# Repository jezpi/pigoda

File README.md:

# pigoda - Introduction
Sensing station project on Raspberry Pi. The project is divided into
software and hardware. The software parts consist of 3 main bits:
daemon called *mqtt_rpi* which runs on raspberry Pi and is used to
send statistics. Application called *mqtt_channel* used to collect
sent statistcs. And the plotting software which are basically shell/python
scripts. The hardware part includes board designs as well as designs of 3D 
printed parts (n/a yet). Everything works via *MQTT* protocol. An example
of MQTT client is available in 

## The software
The standard installation assumes that You have an access to MQTT broker and a
VPS or something like that to collect the statistics. Since I use rrdtool as a plotting
library the statistics require continuity. You should provide a stable connection with accetable
latency (can't be too slow). It is not recommended to run *mqtt_channel* on the same raspberry Pi
where You run *mqtt_rpi* because of SD card overload (It could simply kill Your
SD card). 
### mqtt_rpi
#### Introduction

mqtt_rpi is a broker client as all software pieces written here.
         it sends statistics from previously configured gpios/i2c devices
	 specified in a config file *mqtt_rpi.yaml*. Also it handles some
         basic commands including relay switch on and off.
#### Usage
Normally it is supposed to be invoked via startscript placed in */etc/init.d/pigoda*
It has few useful command line options described below. 
-V Prints build date and time usage() information and then exits with exit(2) code EX_USAGE.
-c Path to config file. If not defined defaults to <code>/etc/mqtt_rpi.yaml</code>
-v Verbose mode. (not implemented yet)
-d Debug mode. (Ditto)
-f Stay in foreground

#### Config file directives:

An example config file included below:
```yaml

%YAML 1.1
---
pidfile: "/var/run/mqtt_rpi.pid"
logfile: "/var/log/mqtt_rpi.log"
debug: 4
daemon: false
delay: 5000000
identity: "mrpi_pooler"
mqtt_host: "localhost"
mqtt_port: 1883
mqtt_user: "mqtt_rpi"
mqtt_password: "CHANGE_ME"
mqtt_keepalive: 120
# configuration of channels
sensors:
        - name: "tempin"
          type: "ds18b20"
          address: "28-00000XXXXXXX"
          channel: "/environment/tempin"
        - name: "tempout"
          type: "ds18b20"
          address: "28-0000XXXXXXXX"
          channel: "/environment/tempout"
        - name: "pressure"
          type: "i2c"
          i2ctype: "bmp85"
          channel: "/environment/pressure"
        - name: "light"
          type: "i2c"
          i2ctype: "pcf8591"
          address: "0x48"
          config: "0"
          channel: "/environment/light"
gpio:
        - name: "green_led"
          gpio_pin: 2
          type: "failure"
        - name: "red_led"
          gpio_pin: 0
          type: "notify"
        - name: "pir_case"
          gpio_pin: 6
          type: "pir_sensor"
        - name: "power button"
          type: "pwr_btn"
          gpio_pin: 5

...

```
Let's describe first set and meaning of system related variables

Variable name | Possible values | Description
--------------|-----------------|------------
pidfile	      | STRING | Includes a valid path in \*NIX like system. Defaults to  > /var/run/mqtt_rpi.pid
logfile       | STRING | Defaults to "/var/log/mqtt_rpi.log"
debug         | NUMERIC | When greater than 0 activates extra debug messages
daemon        | BOOL | daemon mode
delay         | NUMERIC | Defines delay in a pooling loop. Defaults to 5000000

Other variables are related to MQTT connection, like identity user and password used to authenticate on a remote mqtt_host

Variable name | Possible values | Description
--------------|-----------------|------------
identity | STRING | Change this variable in case of having more than one station.
mqtt_host| STRING | A valid FQDN address for *MQTT* broker. Defaults to "localhost".
mqtt_port| NUMERIC | Port number. Defaults to /1883/.
mqtt_user| STRING | User name used to authenticate the client.
mqtt_password| STRING | Password.
mqtt_keepalive| NUMERIC | Delay between keep alive probes
	   
#### Status:
Ready to use version is available. However it's missing some documentation

Part | Task |  Priority | Status
-----|------|-----------|-------
mqtt_rpi, mqtt_channel|Reconnecting on MQTT error | - | Done 
mqtt_rf | Need to integrate with mqtt_rpi | High | Not started
mqtt_pir | Need to integrate with mqtt_rpi | - |  Done
new pigoda v2 board | redesign, include more gpio protection (with optocoupler and or overcurrent protection)| High | design ongoing
website | Make a simple responsive website | High | In progress
mqtt_channel | Change database engine to MySQL from Sqlite3 | Medium | Not started
mqtt_channel | code checkout | Low | Not started
3D models | Models for boxes used to isolate sensors etc. | Low | Not started

### How it really works?!

**The basic knowledge about MQTT protocol is required**
**More info on https://github.com/mqtt/mqtt.github.io/wiki**

There are 4 applications:

* mqtt_rpi - Gets the data from sensors, process it, and publish on a given _MQTT_ channel.
* mqtt_channel -  Listens on a given channel and stores the obtained data to Sqlite3 database.
* mqtt_rf - Gets statistics from  nRF24+ and pushish it on a given _MQTT_ channel.

#### How to use it?
Download the source repository, compile* the sources and install it:

```
git clone https://github.com/jezpi/pigoda
cd mqtt_rpi
make && make install
```

there are some dependencies like libyaml libmosquitto libsqlite3 and libbsd
The application is located in /usr/bin/mqtt_rpi. It installs the configuration
file placed in /etc/mqtt_rpi.yaml. The syntax is a YAML syntax. You need a MQTT
server which defaults to 172.17.17.4, change it to Your server. You have to configure
daemon mode in /etc/mqtt_rpi.yaml ( *mqtt_rpi* does not detach from terminal by default and it prints loads
of debug messages) like this:

<code>
daemon: true
</code>

### mqtt_channel
Ready to use/develop version is available and there's no documentation 

Working version available

### mqtt_pir

Ready to use/develop version is available

### mqtt_rf
Under development (Proof of concept version already works and stores data into db, however
the code needs to be polished a bit)

## The hardware
### pinheader board
In a directory eagle of github repository there are available boards designs ready to fabricate.
The width of connections is thick on purpose. More information will be available soon.

## Notes
It takes 58seconds to start rpi
350mA while it's running and ~400mA on a startup

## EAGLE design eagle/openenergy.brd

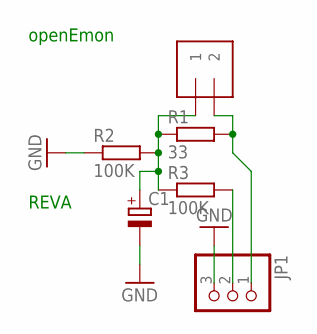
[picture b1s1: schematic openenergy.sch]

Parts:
C1: CPOL-EUB45181A; B45181A
J1: 1X2-3.5MM
JP1: PINHD-1X3; 1X03
R1: 33; 0204/5
R2, R3: 100K; 0204/5

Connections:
GND: C1.-, JP1.3, R2.1
unnamed: C1.+, J1.1, R1.1, R2.2, R3.1
unnamed: J1.2, JP1.1, R1.2
unnamed: JP1.2, R3.2

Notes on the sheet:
openEmon
REVA

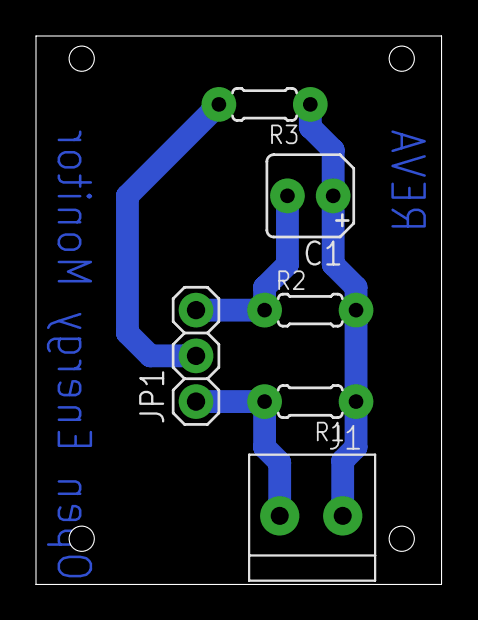
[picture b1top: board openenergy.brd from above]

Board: 2 copper layers, 22.5 x 30.5 mm, 6 parts (0 on the bottom side), 4 nets.

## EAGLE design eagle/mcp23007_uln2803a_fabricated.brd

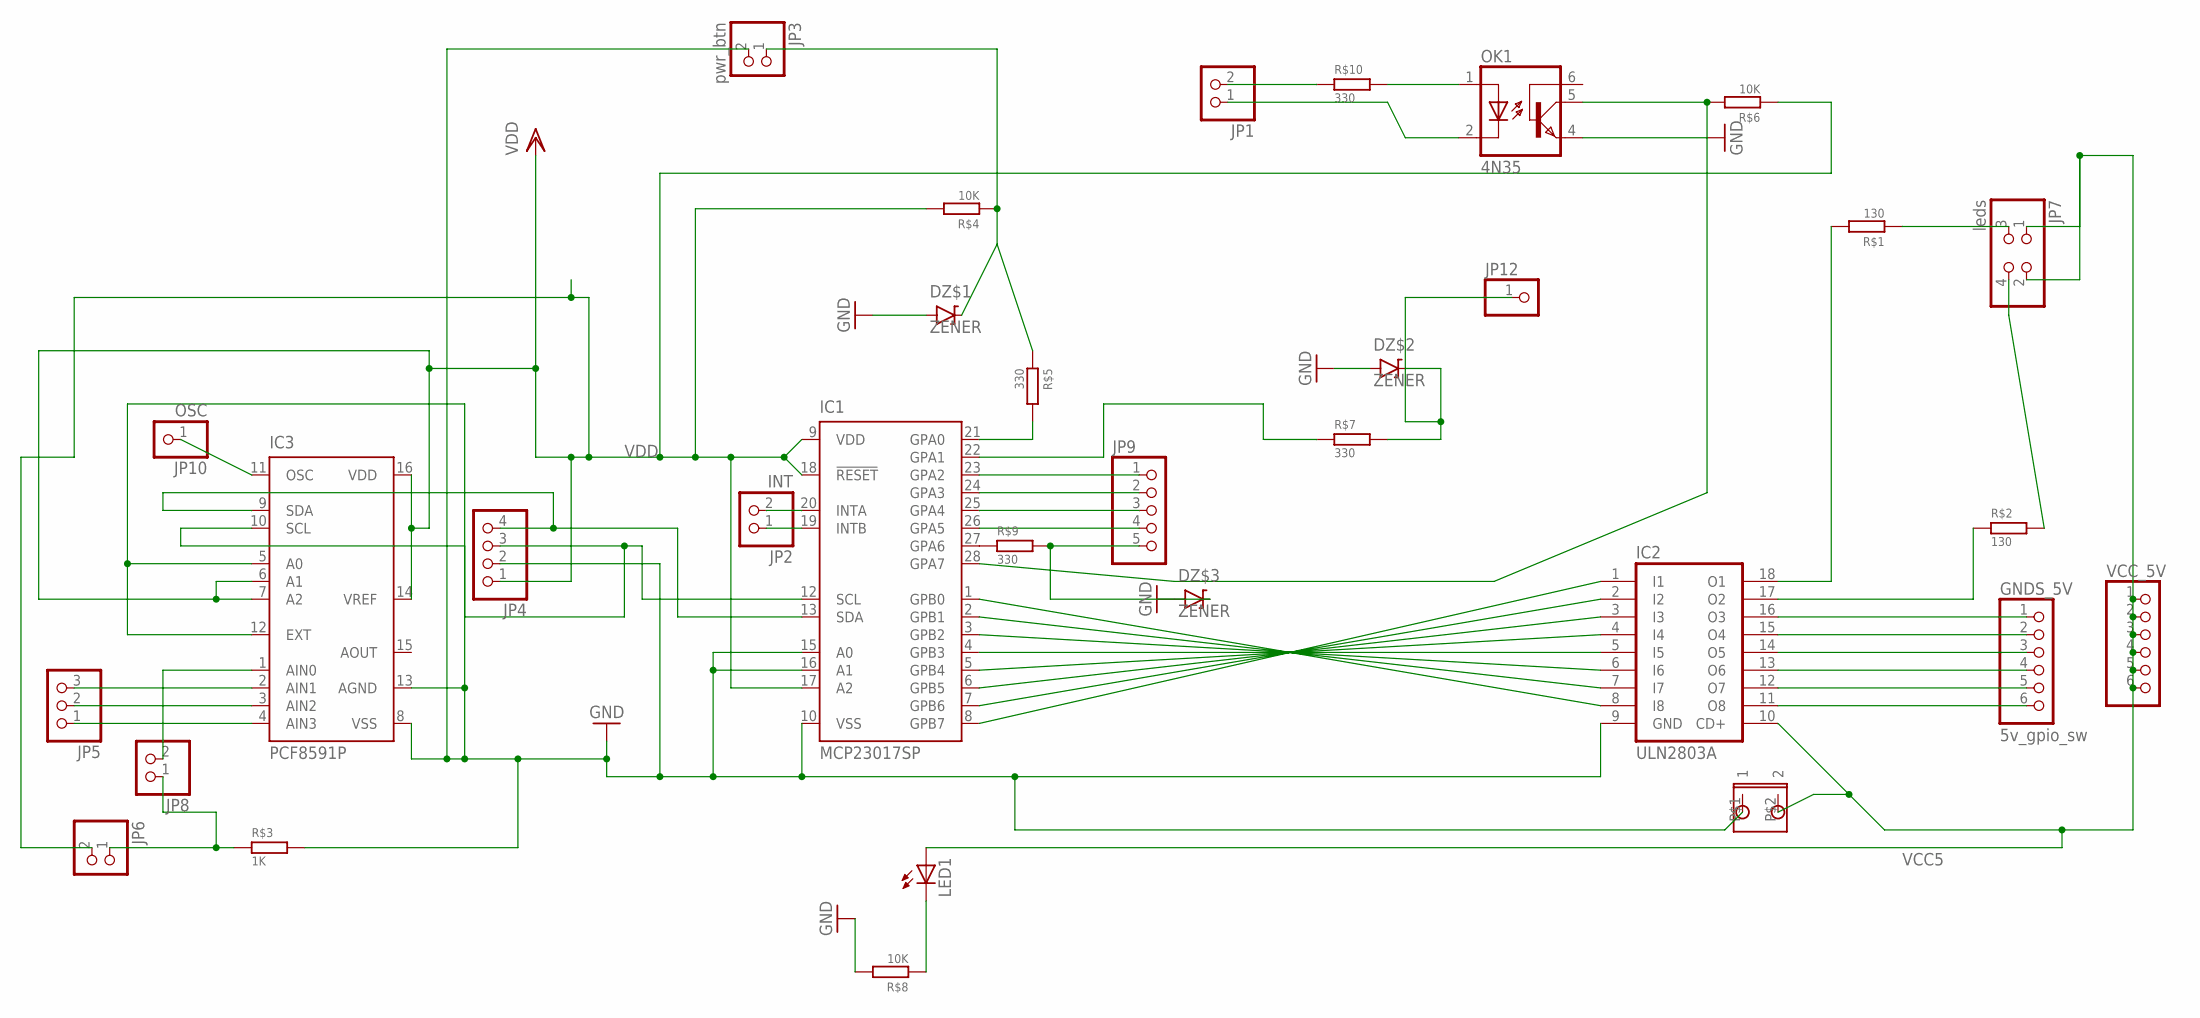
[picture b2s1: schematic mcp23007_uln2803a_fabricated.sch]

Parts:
DZ$1, DZ$2, DZ$3: ZENER
GNDS_5V: 5v_gpio_sw; 1X06
IC1: MCP23017SP; DIL28-3
IC2: ULN2803A; DIL18
IC3: PCF8591P; DIL16
JP1, JP6, JP8: PINHD-1X2; 1X02
JP2: INT; 1X02
JP3: pwr_btn; 1X02
JP4: PINHD-1X4; 1X04
JP5: PINHD-1X3; 1X03
JP7: leds; 2X02
JP9: PINHD-1X5; 1X05
JP10: OSC; 1X01
JP12: PINHD-1X1; 1X01
LED1: LED3MM
OK1: 4N35; DIL06
R$1, R$2: 130; RESISTOR_1/4
R$3: 1K; RESISTOR_1/4
R$4, R$6, R$8: 10K; RESISTOR_1/4
R$5, R$7, R$9, R$10: 330; RESISTOR_1/4
U$1: 5.5MM_PIN
VCC_5V: PINHD-1X6; 1X06

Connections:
GND: DZ$1.P$1, DZ$2.P$1, DZ$3.P$1, IC1.10 (VSS), IC1.15 (A0), IC1.16 (A1), IC2.9 (GND), IC3.5 (A0), IC3.8 (VSS), IC3.12 (EXT), IC3.13 (AGND), JP3.2, JP4.2, OK1.4 (EMI), R$3.P$1, R$8.P$1, U$1.P$1 (1)
unnamed: IC1.1 (GPB0), IC2.8 (I8)
unnamed: IC1.8 (GPB7), IC2.1 (I1)
unnamed: IC1.7 (GPB6), IC2.2 (I2)
unnamed: IC1.2 (GPB1), IC2.7 (I7)
unnamed: IC1.6 (GPB5), IC2.3 (I3)
unnamed: IC1.3 (GPB2), IC2.6 (I6)
unnamed: IC1.5 (GPB4), IC2.4 (I4)
unnamed: IC1.4 (GPB3), IC2.5 (I5)
unnamed: IC1.28 (GPA7), OK1.5 (COL), R$6.P$1
unnamed: IC1.22 (GPA1), R$7.P$2
unnamed: IC1.23 (GPA2), JP9.1
unnamed: IC1.24 (GPA3), JP9.2
unnamed: IC1.25 (GPA4), JP9.3
unnamed: IC1.26 (GPA5), JP9.4
unnamed: IC1.27 (GPA6), R$9.P$2
unnamed: DZ$2.P$2, JP12.1, R$7.P$1
unnamed: IC2.17 (O2), R$2.P$2
unnamed: IC3.11 (OSC), JP10.1
unnamed: GNDS_5V.1, IC2.16 (O3)
unnamed: GNDS_5V.2, IC2.15 (O4)
unnamed: GNDS_5V.3, IC2.14 (O5)
unnamed: GNDS_5V.4, IC2.13 (O6)
unnamed: GNDS_5V.5, IC2.12 (O7)
unnamed: GNDS_5V.6, IC2.11 (O8)
unnamed: DZ$1.P$2, JP3.1, R$4.P$2, R$5.P$2
unnamed: IC1.19 (INTB), JP2.1
unnamed: IC1.20 (INTA), JP2.2
unnamed: IC1.13 (SDA), IC3.9 (SDA), JP4.4
unnamed: IC1.12 (SCL), IC3.10 (SCL), JP4.3
unnamed: IC3.4 (AIN3), JP5.1
unnamed: IC3.3 (AIN2), JP5.2
unnamed: IC3.2 (AIN1), JP5.3
unnamed: IC3.1 (AIN0), JP8.2
unnamed: LED1.K (C), R$8.P$2
unnamed: JP7.3, R$1.P$2
unnamed: IC2.18 (O1), R$1.P$1
unnamed: JP7.4, R$2.P$1
unnamed: DZ$3.P$2, JP9.5, R$9.P$1
unnamed: JP1.2, R$10.P$2
unnamed: OK1.1 (A), R$10.P$1
unnamed: JP6.1, JP8.1, R$3.P$2
unnamed: IC1.21 (GPA0), R$5.P$1
unnamed: JP1.1, OK1.2 (C)
VCC5: IC2.10 (CD+), JP7.1, JP7.2, LED1.A, U$1.P$2 (2), VCC_5V.1, VCC_5V.2, VCC_5V.3, VCC_5V.4, VCC_5V.5, VCC_5V.6
VDD: IC1.9 (VDD), IC1.17 (A2), IC1.18 (!RESET), IC3.6 (A1), IC3.7 (A2), IC3.14 (VREF), IC3.16 (VDD), JP4.1, JP6.2, R$4.P$1, R$6.P$2

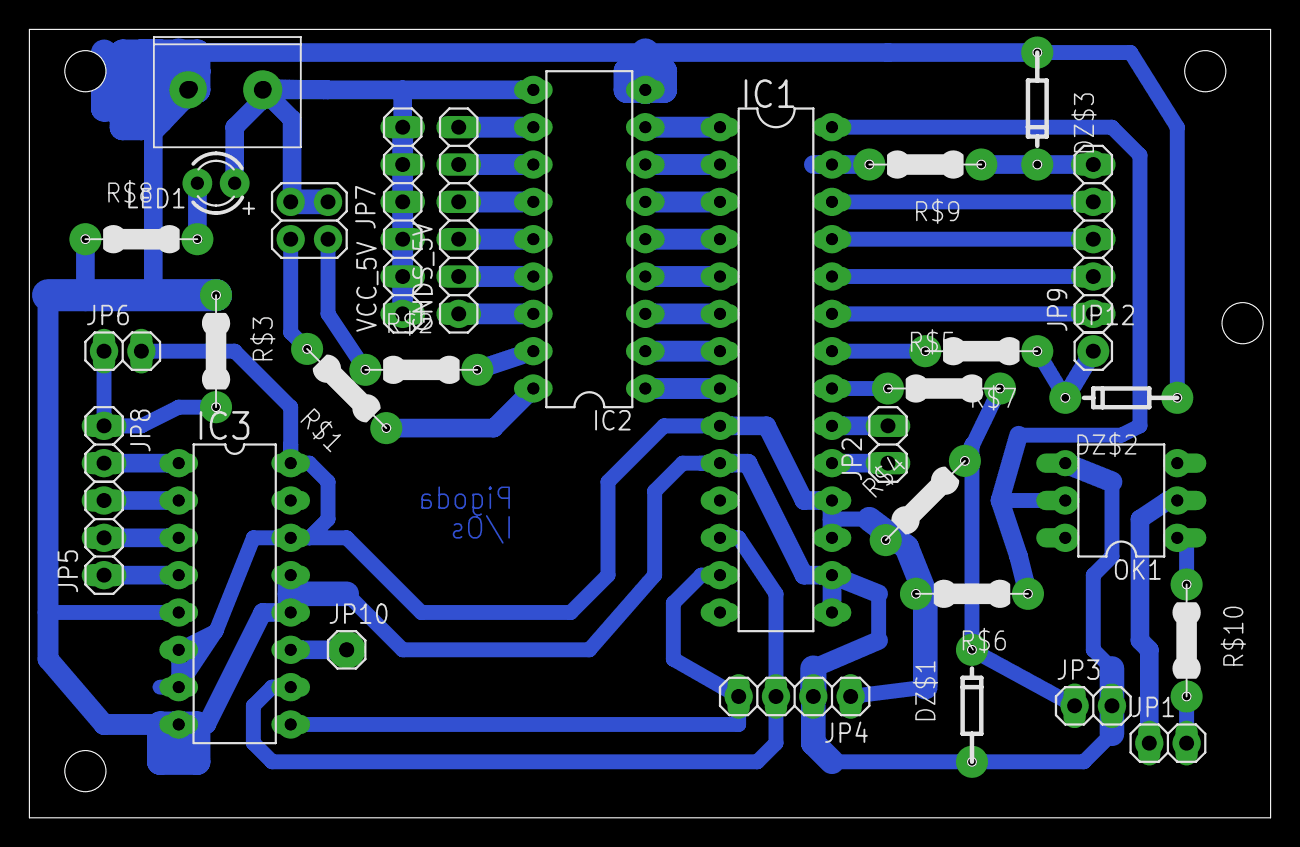
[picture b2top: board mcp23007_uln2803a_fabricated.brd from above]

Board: 2 copper layers, 84.5 x 53.6 mm, 32 parts (0 on the bottom side), 46 nets.

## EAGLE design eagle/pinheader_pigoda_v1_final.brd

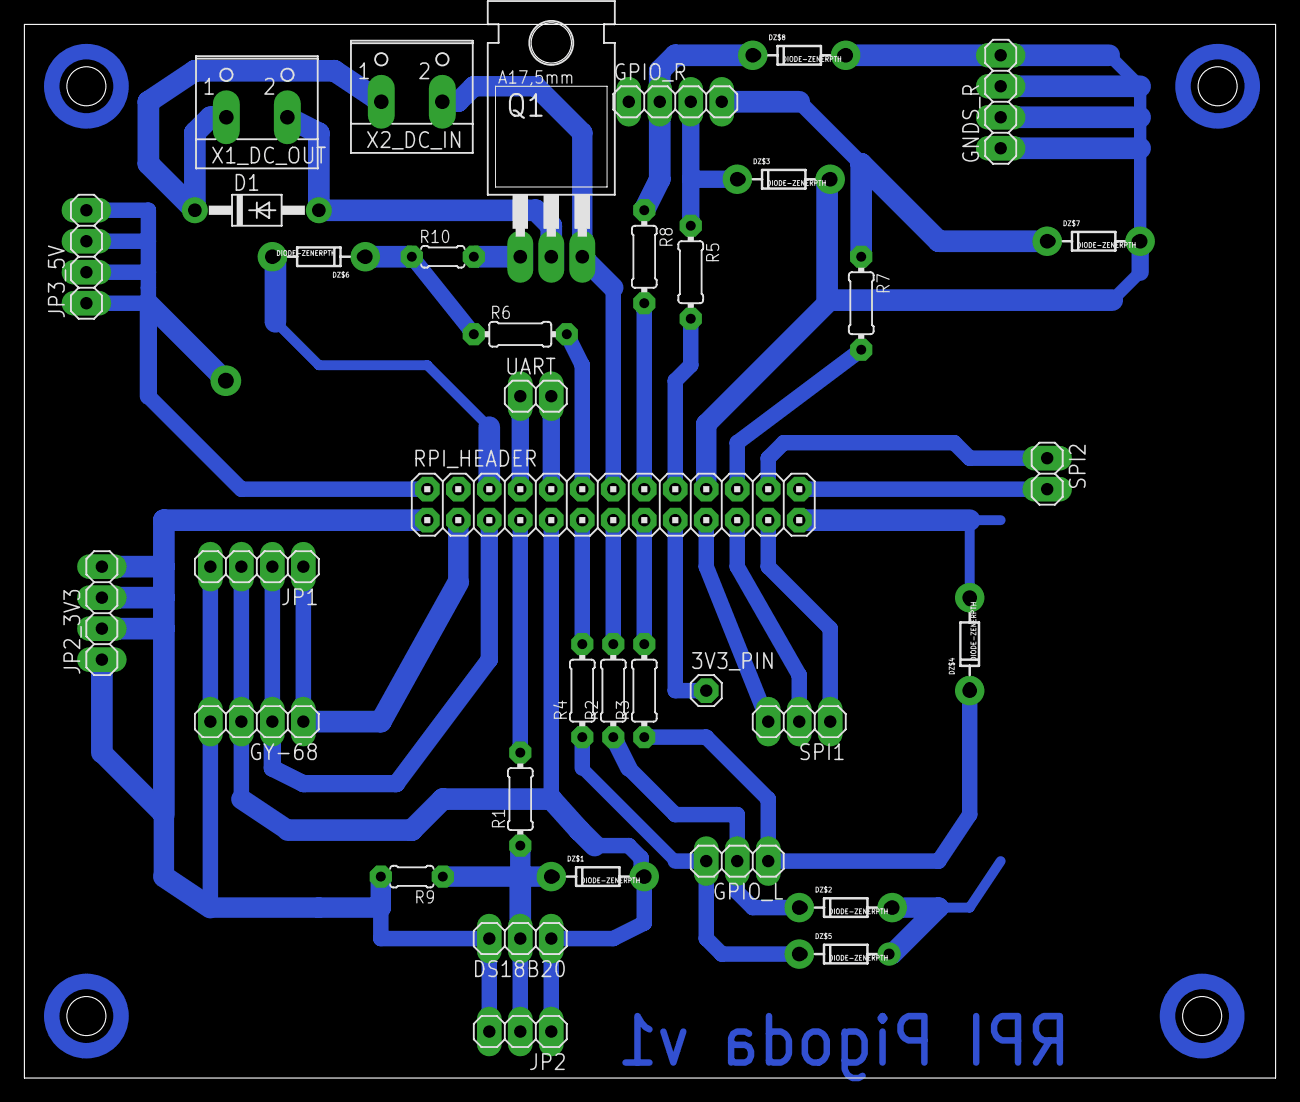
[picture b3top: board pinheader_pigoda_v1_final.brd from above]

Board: 2 copper layers, 102.5 x 86.4 mm, 36 parts (0 on the bottom side), 32 nets.

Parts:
3V3_PIN: 1X01
D1: 1N4004; DO41-10
DS18B20: 1X03
DZ$1, DZ$2, DZ$3, DZ$4, DZ$5, DZ$6, DZ$7, DZ$8: DIODE-ZENERPTH; DIODE-ZENER
GNDS_R: GND; 1X04
GPIO_L: 1X03
GPIO_R: 1X04
GY-68: 1X04
JP1: i2c_ext; 1X04
JP2: 1X03
JP2_3V3: 3v3_vcc; 1X04
JP3_5V: 5v_vcc; 1X04
Q1: TIP120; TO220AH
R1: 0204/7
R2, R3, R4, R5, R6, R7, R8: 330; 0204/7
R9: 4k7; 0204/5
R10: 0204/5
RPI_HEADER: 2X13
SPI1: 1X03
SPI2: 1X02
UART: 1X02
X1_DC_OUT, X2_DC_IN: W237-102

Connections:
+3V3: DS18B20.3, GY-68.4, JP1.4, JP2.3, JP2_3V3.1, JP2_3V3.2, JP2_3V3.3, JP2_3V3.4, R9.2, RPI_HEADER.1
+5V: JP3_5V.1, JP3_5V.2, JP3_5V.3, JP3_5V.4, RPI_HEADER.2
+12V: D1.C, X1_DC_OUT.1, X2_DC_IN.1
GND2: DS18B20.1, DZ$1.P$2, DZ$2.P$2, DZ$3.P$2, DZ$4.P$2, DZ$5.P$2, DZ$6.P$2, DZ$7.P$2, DZ$8.P$2, GNDS_R.1, GNDS_R.2, GNDS_R.3, GNDS_R.4, GY-68.3, JP1.3, JP2.1, Q1.E, RPI_HEADER.6, RPI_HEADER.9, RPI_HEADER.14, RPI_HEADER.20, RPI_HEADER.25, X2_DC_IN.2
unnamed: DZ$2.P$1, GPIO_L.2, R2.1
unnamed: DS18B20.2, DZ$1.P$1, JP2.2, R1.1, R9.1
unnamed: R1.2, RPI_HEADER.7
unnamed: DZ$4.P$1, GPIO_L.1, R3.1
unnamed: RPI_HEADER.23, SPI1.1
unnamed: DZ$5.P$1, GPIO_L.3, R4.1
unnamed: R4.2, RPI_HEADER.11
unnamed: R2.2, RPI_HEADER.13
unnamed: R3.2, RPI_HEADER.15
unnamed: Q1.B, R10.2
unnamed: GY-68.1, JP1.1, RPI_HEADER.3
unnamed: 3V3_PIN.1, RPI_HEADER.17
unnamed: DZ$3.P$1, GPIO_R.3, R5.1
unnamed: RPI_HEADER.8, UART.1
unnamed: RPI_HEADER.10, UART.2
unnamed: DZ$6.P$1, R6.1, R10.1
unnamed: DZ$7.P$1, GPIO_R.4, R7.1
unnamed: DZ$8.P$1, GPIO_R.2, R8.1
unnamed: R6.2, RPI_HEADER.12
unnamed: R5.2, RPI_HEADER.18
unnamed: R7.2, RPI_HEADER.22
unnamed: R8.2, RPI_HEADER.16
unnamed: RPI_HEADER.21, SPI1.2
unnamed: RPI_HEADER.24, SPI2.1
unnamed: RPI_HEADER.26, SPI2.2
unnamed: RPI_HEADER.19, SPI1.3
unnamed: GY-68.2, JP1.2, RPI_HEADER.5
unnamed: D1.A, Q1.C, X1_DC_OUT.2

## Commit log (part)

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2016-05-30 Test
2016-05-30 init
2016-05-31 Create gh-pages branch via GitHub
2016-06-04 removed unnecessary files
2016-06-05 changed default path of sqlite3db
2016-06-05 resolve problem with "Program received signal SIGILL, Illegal instruction."
2016-06-05 fixed a NULL pointer bug
2016-06-05 fixed old dependencies of mqtt_rpi
2016-06-05 return after config file parsing failure
2016-06-05 changed default sqlite3 db path and rrd databases path to /var/db/rrdcache and /var/db/pigoda
2016-06-05 path change of rrd files and change of name conventions
2016-06-05 changed config file default path to a proper one /etc/mqtt_channel instead of mqtt_rpi.yaml
2016-06-05 pir sensor init
2016-06-05 removed duplicated code
2016-06-05 continuation of code reducion
2016-06-06 documentation bits
2016-06-14 enable core dumps
2016-06-17 added a "hidden" timeout used to wait for a network interface. Without it the mqtt_rpi is returning with an sockerror.
2016-06-17 new function flash_led added
2016-06-17 status functionality added
2016-06-17 added support for mq2 sensor. However its the last one before big change. The plan is to listen on a given channel and store _everyting_ what appears on a given subject without any distinction in mqt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
2016-06-23 network failure indication
2016-06-23 changed delay of led action (the intention is to wait for network interface and so on. It just indicates the need to introduce reconnect feature
2016-06-23 restart option
2016-06-23 removed NULL pointer reference in fclose call
2016-06-23 added svg illustration of my MQTT implementation and TODO list
2016-06-23 More tasks and "How it really works" bits
2016-06-28 command list ordered
2016-11-03 sync
2016-11-03 'fixed the mess with header files by removing spare reference to mqttc.h which wasn't in use and was creating unnecesary confusion. Added option "delay" to the config file.'
2016-11-03 added option delay
2016-11-03 changed default broker address
2016-11-03 changed default address
2016-11-08 Added option stop to stop the deamon and option runlocal to run it localy
2016-11-08 More messages on connection problems
2016-11-08 changed TS values to float (actually what it is)
2016-11-08 reconnect feature ported from mqtt_rpi
2016-11-08 changed paths
2016-11-08 changed default paths. Added support for a little config file
2016-11-08 update of default paths
2016-11-10 problem with connection to broker which is using authentication. This is just a code sync.
2016-11-10 added a simple mosquittolib code for test purposes
2016-11-10 connection failure error handling. I did a bit of disaster, anyway, i'm about to fix it now :)
2016-11-10 mosquittolib testing code.
2016-11-10 makefile gdb ext and dependency for runlocal
2016-11-10 missing constants
2016-11-10 little arg improvments
2016-11-10 fixed problem with connection. There were missing arguments to mosquitto_username_pw_set
2016-11-11 standarised the value "run" with mqtt_channel and added more user friendly information to stop section
2016-11-11 removed some code ancestries
2016-11-11 startup_led_act added another argument responsible for blink delay
2016-11-11 declaration update
2016-11-11 invalid preprocesor directives
2016-11-11 disable thingspeak by default
2016-11-11 alsa_mic_mqtt.c
2016-11-12 got rid of some old and deprecated nomenclature
2016-11-12 added getopt support, removed hardcoded passwords and stuff. Connection error handling and publishing to a new channel
2016-11-12 important changes! Some code is broken! Added an option to change path of sqlite3db and mqtt_poli_proc_msg
2016-11-12 Introduced MQTT_poli_store. Feature of storing all incoming data on a given channel to sqlitedb
2016-11-12 added support for getopt
2016-11-12 simplified the code. Standarized sqlite table schemas
2016-11-12 standarized the code with table schemas
2016-11-12 supressed some debug messages and added feature of debug print
2016-11-15 added section to install all dependencies
2016-11-15 dynamic sensor support
2016-11-15 dynamic sensor handling in parser
2016-11-15 sensor initialization. "dynamic sensor"
2016-11-15 updated strtok. included a proper header
2016-11-15 Identity failure. I found an "unusual" problem with MQTT broker connection. Two identical identities are not allowed to connect. So i added such feature to change in the config file the MQTT identity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
2016-11-15 Changed constants for default pin. Fixed bug with mqtt_user given in place of mqtt_host. Added more command line options to tune the tool. Added the possibility to change MQTT identity
2016-11-15 added tempin_guerni and execution without calling the script from interpreter
2016-11-15 Added support of new config file option "identity". It was introduced to avoid confusion between same instances of mqtt_channel client connected to the broker. In case of using same identity both cli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
2016-11-15 added functionality of automated creation of tables in a given sqlite3 db
2016-11-16 finally making all graphs totally dinamic
2016-11-16 removed code responsable for vc_temp updating. As well as tried to resolve problem with crashing rrdupdate. The reason is probably duplicated records for a given timestamp in sqlitedb
2016-11-16 thingspeak dependencies removed. Added installation of all needed debian dependencies
2016-11-16 included a function to create table on fly
2016-11-16 setting default arguments to a local config file
2016-11-16 added build of alsamicmqtt
2016-11-16 removed not used file
2016-11-16 introduced usage() function to print the whole command line arguments usage
2016-11-16 removed all unnecesary files responsable for plotting rrd graphs and coping data between sqlite3 and rrd db
2016-11-16 removed more unnecesary files
2016-11-16 fixed a duplicated path to graphs
2016-11-16 Updated deprecated nomenclature.
2016-11-16 dont panic with rrdtool.update failures
2016-11-16 graphd - rrdtool graph daemon
2016-11-16 added lastupdate time for each type of data
2016-11-16 addrs
2016-11-16 removed unnecesary code
2016-11-17 introduced led configuration
2016-11-20 removed structures related to parser and sensor configuration from main header file
2016-11-20 parsing options for gpios like pin number and builtin function
2016-11-20 introduction of dynamic gpio configuration. as said via config file
2016-11-20 gpios configurable via config file
2016-11-20 distincion between main program constants and parsers stuff
2016-11-20 some fixes. I commited the code without compiling it. It was just a sync mass-commit. Now Im going to fix in on my rpi
2016-11-20 configuration of gpios via yaml config file deploied!
2016-11-20 power button function. Early devel-stage, not well wrapped
2016-11-20 adding makefile
2016-11-21 new board
2016-11-26 fixed bug which occured while updating non-existent rrd files. Added functions from fill_db.py used to created a missing rrd file
2016-11-26 fixed pressure graphs
2016-11-26 availability to query more pcf8591 analog inputs
2016-11-27 introduced topic for gpios. Still it is not 100% functional
2016-11-27 pir sensor configuration included!
2016-11-28 customized pir sensor graphs
2016-11-28 added links to custom graphs
2016-11-28 added link to github
2016-11-28 reconnecting on EHOSTUNREACH
2016-11-29 script used to removed unnecesary data sets
2016-12-02 added some functionality to the daemon. Now I think I can use more MQTT protocol and concept of controlling the status of all daemons sould be implemented (since i use more than 2 daemons in MQTT net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
2016-12-02 graph adjustments. Preparint to create automatic weekly/daily and custom graphs
2016-12-06 removed trump from code and added getopt(3) support. Some flags are missing
2016-12-06 debugging mqtt_pir issue and added support for -c option which is used to specify a path to config file
2016-12-06 Resolved 2 bugs which are following and added some new functionality improvments. 1) Problem with pir sensor activation - It didn't get activated unless the led was configured 2) Problem with get_tem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
    Improvments:
    1) Added -f flag to stay in foreground
    2) From now sensor failure would be reported to the log file
    and some messages are more descriptive.
2016-12-06 script used to report vc_temp on rpi
2016-12-08 Updated the usage message to commands version|restart. Added an version command which simply uses option -V to display version and build date/time
2016-12-08 restarting connection on more network failures as well as displaying all build flags while using -V flag. Updated init log message to build time
2016-12-09 config for relay
2016-12-09 new config for tip120 and relay
2016-12-09 handling for mcp23007
2016-12-09 relay_ctl()
2016-12-10 Updated information about mqtt_rpi
2016-12-10 installation of all html files. Taking install path from env
2016-12-10 expired stuff
2016-12-10 truly customized graphs here
2016-12-10 changed default graph path to /var/www/pigoda and export of env variable from RRD_GRAPH_PATH to PNG_GRAPH_PATH
2016-12-10 Among many changed what was the main subject of work was adding monthly and weekly graphs. Daily graphs remain not published on a website
2016-12-10 some debug message and graphing daily stats
2016-12-11 included bootstrap and daily automatic graphs
2016-12-11 installing static html files in given installpath
2016-12-11 daily statistics included
2016-12-11 changed name to header.html
2016-12-11 changed the name of variable and exported to env to be used with make(1)
2016-12-11 added function to update graph list and generate html
2016-12-11 footer changed to stay and the end of the whole website instead of being stick to bottom part of the window
2016-12-12 changed the front page
2016-12-12 some changes in graph list. Putting all graphs in the separated boxes
2016-12-12 control of output messages
2016-12-12 actualization of graphing.sh commands inside of graphingd.sh
2016-12-12 removed "site generated" messages
2016-12-14 removed an ugly svg image which was illustrating how it works. Changed description a little bit. Updated the todo list
2016-12-14 changed the description of 3 headings
2016-12-14 page header included
2016-12-14 added -C option to specify number of channels for alsa dev
2016-12-14 changes in mqtt_channel! Finally it accepts the channel configuration from the config file. It divides the print messages into ones which are valuable and ones which are debbuging only. I plan to rem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
2016-12-14 moved most structures to mqtt.h
2016-12-14 sqlite3 debug...
2016-12-14 got rid of this useless stuff
2016-12-14 code cleanup
2016-12-15 added separation of all ADTs
2016-12-15 moved ADTs to a separated file
2016-12-15 exported ADTs
2016-12-15 changed default db path
2016-12-15 changed default behavior, not drawing weekly and monthly statistics in a daemon mode
2016-12-17 adding some javascripts to make the website more interactive
2016-12-17 changed htmls for a graph picture
2016-12-17 syncing features
2016-12-17 added support for cookies and more personalized views
2016-12-18 custom graphs added
2016-12-18 included site header in git repository
2016-12-18 fixed some installation issues. like dependencies of js libraries
2016-12-18 missing header for ADTs
2016-12-18 export of more paths
2016-12-19 fabricated boards
2016-12-20 installation of bootstrap
2016-12-20 exporting alsao RRD_DB_PATH
2016-12-20 schematics taken from open energy
2016-12-21 changed descriptions
2016-12-21 tool which is going to supress graphing.sh
2016-12-21 bool type for failure
2016-12-21 stdbool included. header updated
2016-12-22 customized custom graphs
2016-12-23 yaml highlighting
2016-12-23 added description of some base config file variables
2016-12-23 Removed some unnecesary stuff
2016-12-27 changed logging options. Solved bug with disconnect_callback
2016-12-28 added support for exclude list
2016-12-28 added TP_LOG responsible for logging data to logfile
2016-12-28 changed styling of messages to make it more readable. Logging of MQTT communication only in verbose mode (-v option)
2016-12-29 adjusted some log messages
2017-01-01 added support for json
2017-02-07 monthly graphs with day number
2023-07-20 Fixing error Too many open files
    missing fclose
    09:37:17 20-07 Failed to read /sys/bus/w1/devices/28-0000055a8be7/w1_slave Too many open files
    09:37:17 20-07 "tempin" query failure
    09:37:17 20-07 failed to pool sensors. Pooling disabled
    09:40:27 20-07 MQTT_loop(): 22
2023-07-20 light variable not used
2023-07-20 using the syscall instead stdio
2023-07-20 casting void * to char *
